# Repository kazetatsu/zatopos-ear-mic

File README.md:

# zatopos-ear-mic
KiCad  project: PCB with two micrphones &amp; one A/D converter, for zatopos-ear

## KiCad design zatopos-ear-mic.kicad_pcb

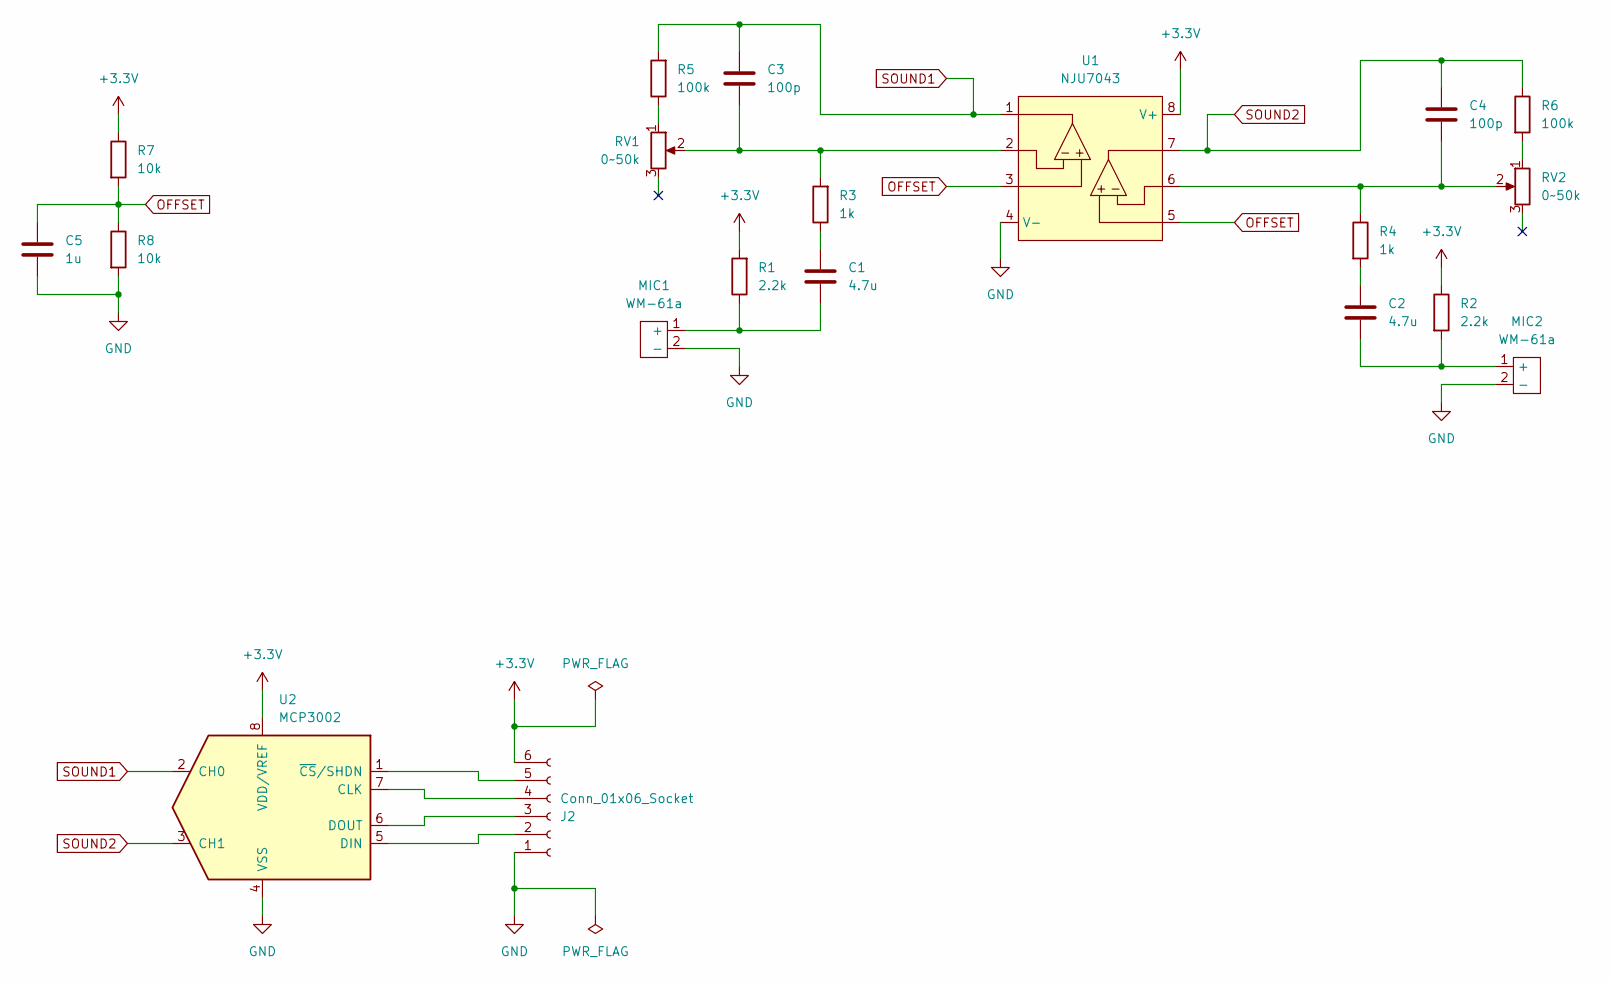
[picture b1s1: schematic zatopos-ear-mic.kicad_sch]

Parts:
C1, C2: 4.7u; C_0603_1608Metric; LCSC PN C19666
C3, C4: 100p; C_0603_1608Metric; LCSC PN C14858
C5: 1u; C_0603_1608Metric; LCSC PN C15849
J2: Conn_01x06_Socket; JST_XH_B6B-XH-A_1x06_P2.50mm_Vertical
MIC1, MIC2: WM-61a
R1, R2: 2.2k; R_0603_1608Metric; LCSC PN C4190
R3, R4: 1k; R_0603_1608Metric; LCSC PN C21190
R5, R6: 100k; R_0603_1608Metric; LCSC PN C25803
R7, R8: 10k; R_0603_1608Metric; LCSC PN C25804
RV1, RV2: 0~50k; GF063P
U1: NJU7043; DIP-8_W7.62mm_Socket
U2: MCP3002; DIP-8_W7.62mm_Socket

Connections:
+3.3V: J2.6, R1.2, R2.1, R7.1, U1.8 (V+), U2.8 (VDD/VREF)
GND: C5.2, J2.1, MIC1.2 (-), MIC2.2 (-), R8.2, U1.4 (V-), U2.4 (VSS)
unnamed: C1.1, R3.1
unnamed: C2.1, R4.2
unnamed: J2.2, U2.5 (DIN)
unnamed: J2.3, U2.6 (DOUT)
unnamed: J2.4, U2.7 (CLK)
unnamed: J2.5, U2.1 (~CS/SHDN)
unnamed: C1.2, MIC1.1 (+), R1.1
unnamed: C2.2, MIC2.1 (+), R2.2
unnamed: R5.1, RV1.1
unnamed: R6.2, RV2.1
unnamed: C3.2, R3.2, RV1.2, U1.2 (A_IN-)
unnamed: C4.2, R4.1, RV2.2, U1.6 (B_IN-)
OFFSET: C5.1, R7.2, R8.1, U1.3 (A_IN+), U1.5 (B_IN+)
SOUND1: C3.1, R5.2, U1.1 (A_OUT), U2.2 (CH0)
SOUND2: C4.1, R6.1, U1.7 (B_OUT), U2.3 (CH1)

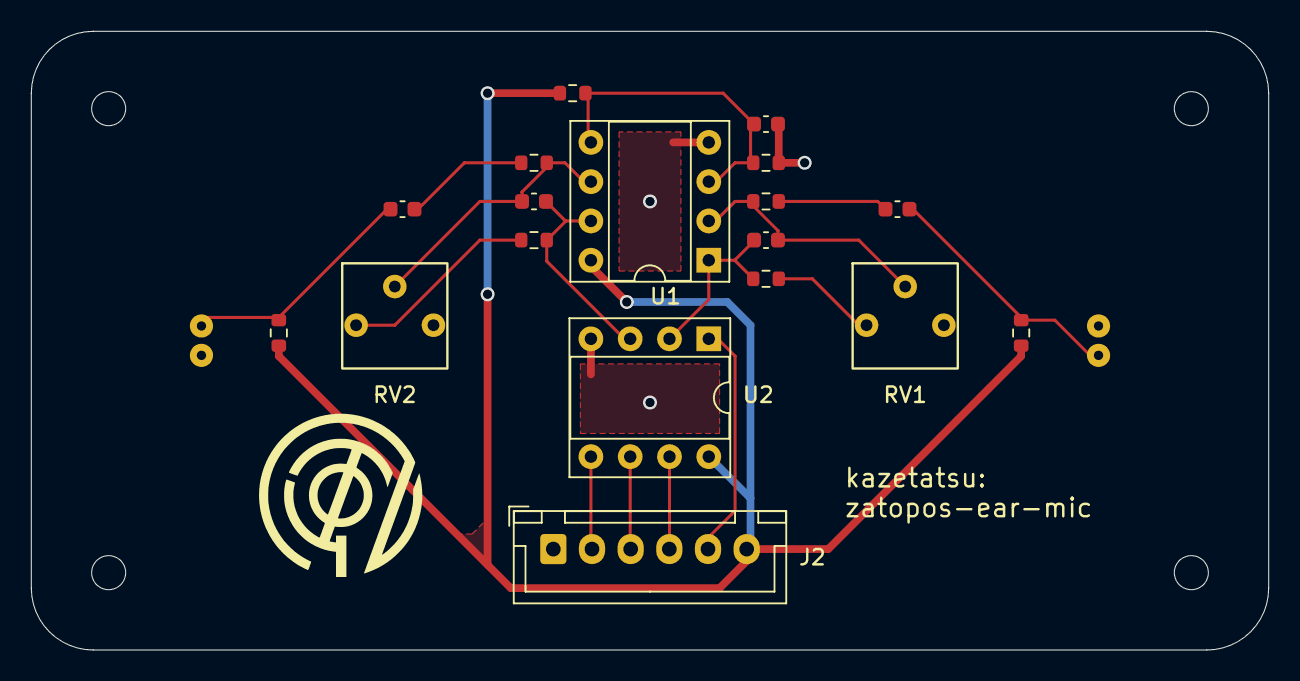
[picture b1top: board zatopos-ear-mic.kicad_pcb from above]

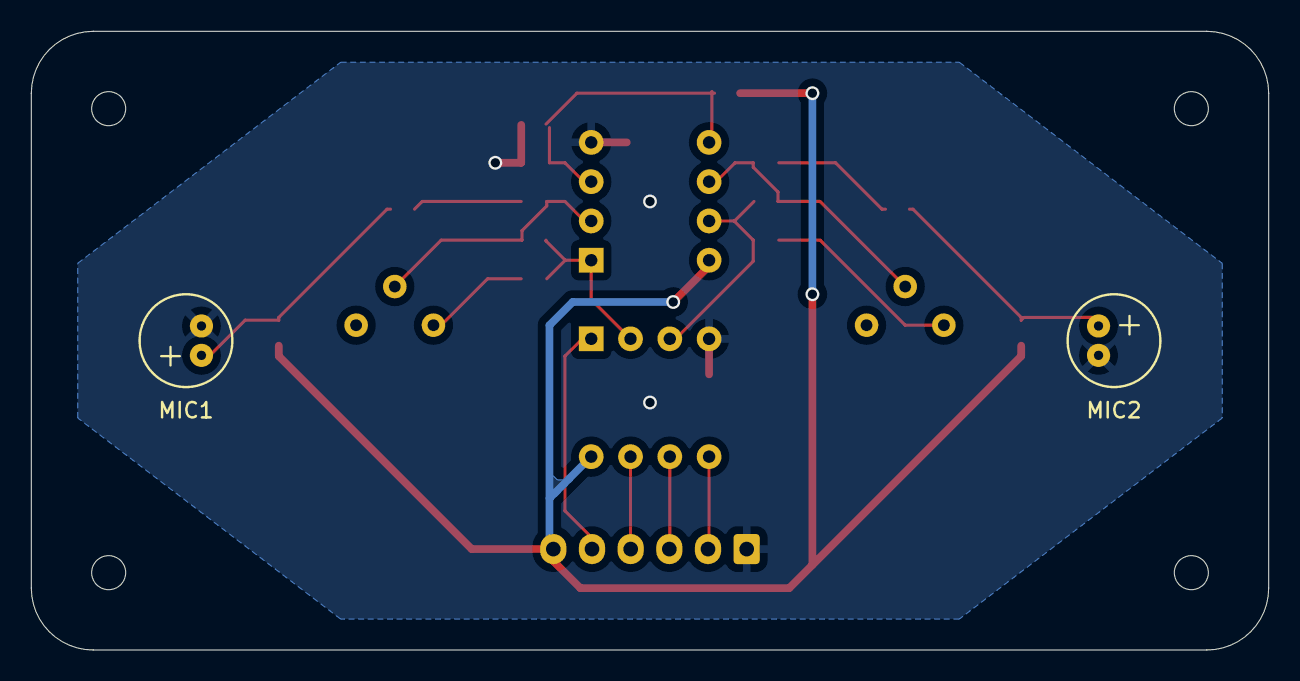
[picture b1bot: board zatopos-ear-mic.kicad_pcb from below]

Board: 2 copper layers, 80.0 x 40.0 mm, 20 parts (2 on the bottom side), 17 nets.

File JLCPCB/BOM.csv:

Comment,Designator,Footprint,LCSC PN
4.7u,"C1,C2",Capacitor_SMD:C_0603_1608Metric,C19666
100p,"C3,C4",Capacitor_SMD:C_0603_1608Metric,C14858
1u,C5,Capacitor_SMD:C_0603_1608Metric,C15849
2.2k,"R1,R2",Resistor_SMD:R_0603_1608Metric,C4190
1k,"R3,R4",Resistor_SMD:R_0603_1608Metric,C21190
100k,"R5,R6",Resistor_SMD:R_0603_1608Metric,C25803
10k,"R7,R8",Resistor_SMD:R_0603_1608Metric,C25804

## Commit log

2024-10-28 Add symbols (WM-61a, NJU7043, NJU77552)
2024-10-28 Draw circuit
2024-10-28 Fix ERC errors
2024-10-30 Add footprints (B6B-XH-A, GF063P, WM-61a)
2024-10-30 Assign footprints
2024-10-30 Write caption
2024-10-30 Add a footprint: logo_kaze
2024-10-30 Place footprints
2024-10-30 Connect footprints
2024-10-30 Solve errors: not connected
2024-10-30 Small change place
2024-10-30 Change constraits acording to JLCPCB
2024-10-30 Change text thickness of silkscreen
2024-10-30 Write caprion
2024-10-30 Change wire, place: shorter path & less corner
2024-10-30 Change wire, place: less corner
2024-10-30 Plot gerber files
2024-10-31 Change footprints to JLCPCB basic parts
2024-10-31 Replace footprints
2024-10-31 Change place: OPamp and registers closer
2024-10-31 Regenerate Gerber files
2024-10-31 Not ignore .csv files
2024-10-31 Add files to order JLCPCB to PCBA
